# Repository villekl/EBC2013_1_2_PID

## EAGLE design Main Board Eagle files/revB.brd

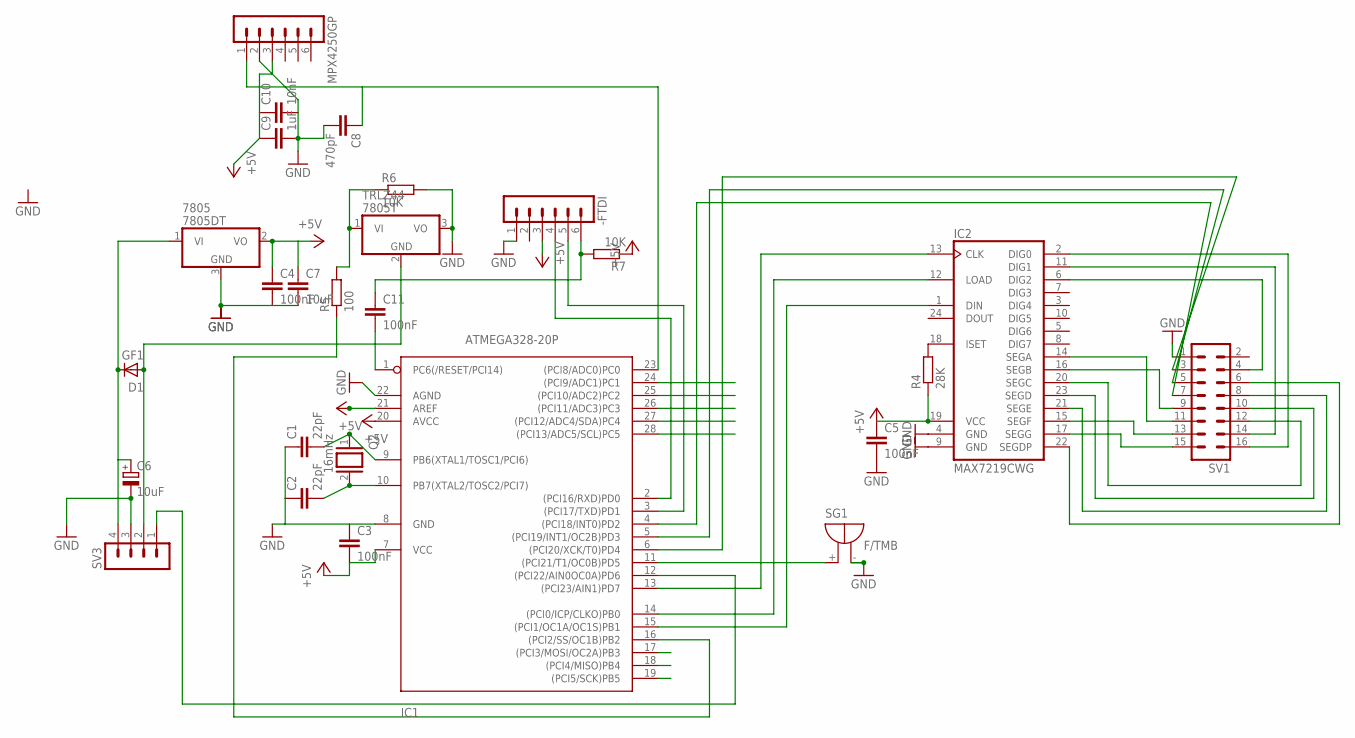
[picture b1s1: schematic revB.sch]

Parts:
7805: 7805DT; TO252
-FTDI: MA06-1
C1, C2: 22pF; C0805; MPN ERB21B5C2D220JDX1L
C3, C4, C5, C11: 100nF; C0805; MPN C0805X104K5RACTU
C6: 10uF; E2,5-6E
C7: 10uF; C0805; MPN C0805X104K5RACTU
C8: 470pF; C0805; MPN C0805X104K5RACTU
C9: 1uF; C0805; MPN C0805X104K5RACTU
C10: 10nF; C0805; MPN C0805X104K5RACTU
D1: GF1; SMA-DO214AC
IC1: ATMEGA328-20P; DIL28-3
IC2: MAX7219CWG
MPX4250GP: MA06-1
Q2: 16mHz; QS; MPN 16.000MHZ HC49/4H/30/50/40/18PF/ATF
R4: 28K; R0805
R5: 100; R0805
R6, R7: 10K; R0805
SG1: F/TMB
SV1: MA08-2
SV3: MA04-1
TRLZ44: 7805T; TO220H

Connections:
+5V: 7805.2 (VO), -FTDI.3, C3.2, C4.1, C5.1, C7.1, C9.1, C10.1, IC1.7 (VCC), IC1.20 (AVCC), IC1.21 (AREF), IC2.19 (VCC), MPX4250GP.3, R4.1, R7.1
GND: 7805.3 (GND), -FTDI.1, C1.1, C2.1, C3.1, C4.2, C5.2, C6.-, C7.2, C8.2, C9.2, C10.2, IC1.8 (GND), IC1.22 (AGND), IC2.4 (GND), IC2.9 (GND), MPX4250GP.2, R6.2, SG1.-, SV1.1, SV3.3, TRLZ44.3 (VO)
unnamed: C1.2, IC1.9 (PB6(XTAL1/TOSC1/PCI6)), Q2.1
unnamed: R5.2, R6.1, TRLZ44.1 (VI)
unnamed: IC1.15 ((PCI1/OC1A/OC1S)PB1), IC2.1 (DIN)
unnamed: IC2.6 (DIG2), SV1.4
unnamed: IC2.11 (DIG1), SV1.14
unnamed: IC2.22 (SEGDP), SV1.6
unnamed: IC2.21 (SEGE), SV1.8
unnamed: C8.1, IC1.23 ((PCI8/ADC0)PC0), MPX4250GP.1
unnamed: IC2.23 (SEGD), SV1.10
unnamed: IC2.20 (SEGC), SV1.12
unnamed: IC2.2 (DIG0), SV1.16
unnamed: IC2.17 (SEGG), SV1.15
unnamed: IC2.15 (SEGF), SV1.13
unnamed: IC2.14 (SEGA), SV1.11
unnamed: IC2.18 (ISET), R4.2
unnamed: IC1.16 ((PCI2/SS/OC1B)PB2), R5.1
unnamed: IC1.14 ((PCI0/ICP/CLKO)PB0), IC2.12 (LOAD)
unnamed: IC1.13 ((PCI23/AIN1)PD7), IC2.13 (CLK)
unnamed: IC1.4 ((PCI18/INT0)PD2), SV1.7
unnamed: IC1.5 ((PCI19/INT1/OC2B)PD3), SV1.5
unnamed: IC1.6 ((PCI20/XCK/T0)PD4), SV1.3
unnamed: IC1.11 ((PCI21/T1/OC0B)PD5), SG1.+
unnamed: -FTDI.6, C11.1, R7.2
unnamed: -FTDI.4, IC1.2 ((PCI16/RXD)PD0)
unnamed: -FTDI.5, IC1.3 ((PCI17/TXD)PD1)
unnamed: 7805.1 (VI), C6.+, D1.K (C), SV3.4
unnamed: C2.2, IC1.10 (PB7(XTAL2/TOSC2/PCI7)), Q2.2
unnamed: D1.A, SV3.2, TRLZ44.2 (GND)
unnamed: IC1.12 ((PCI22/AIN0OC0A)PD6), SV3.1
unnamed: IC2.16 (SEGB), SV1.9
unnamed: C11.2, IC1.1 (PC6(/RESET/PCI14))

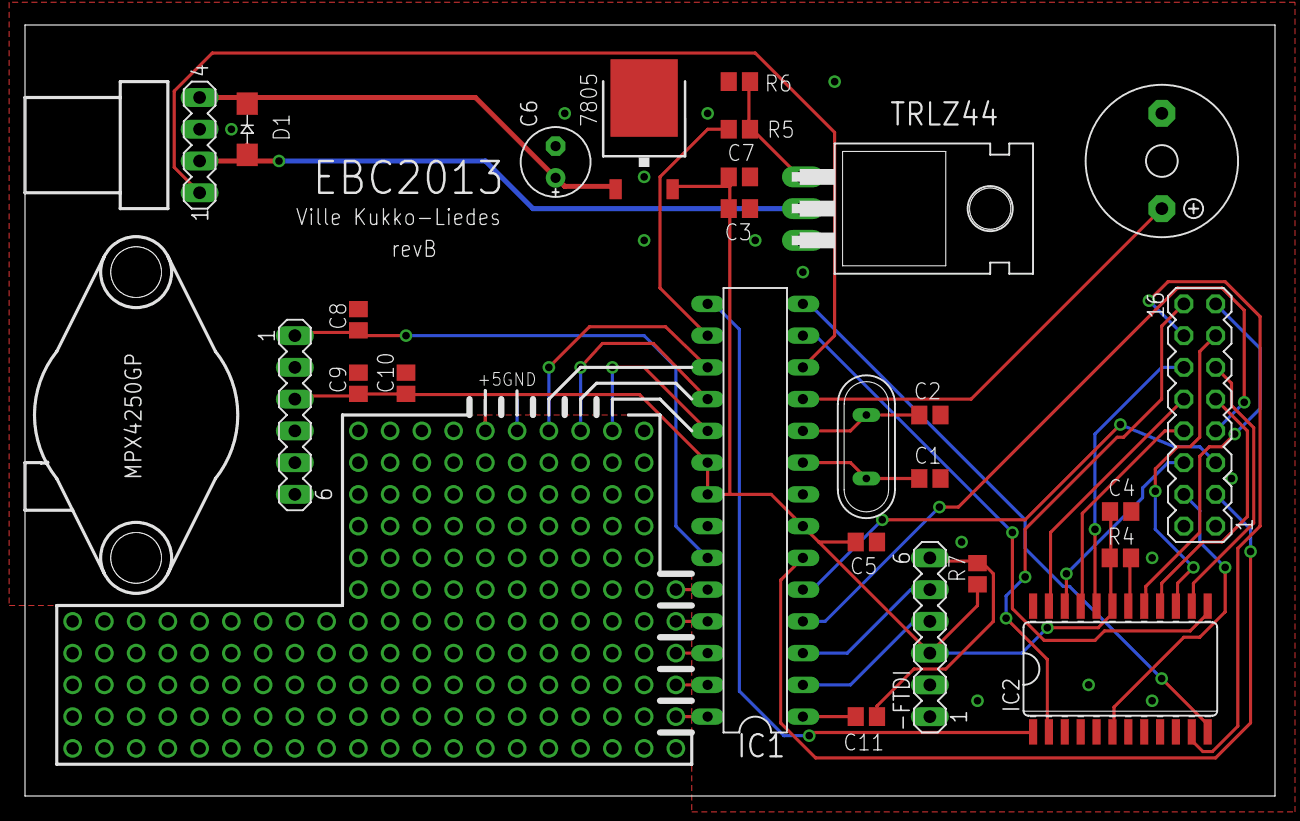
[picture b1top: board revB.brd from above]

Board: 2 copper layers, 100.0 x 61.7 mm, 26 parts (0 on the bottom side), 33 nets.

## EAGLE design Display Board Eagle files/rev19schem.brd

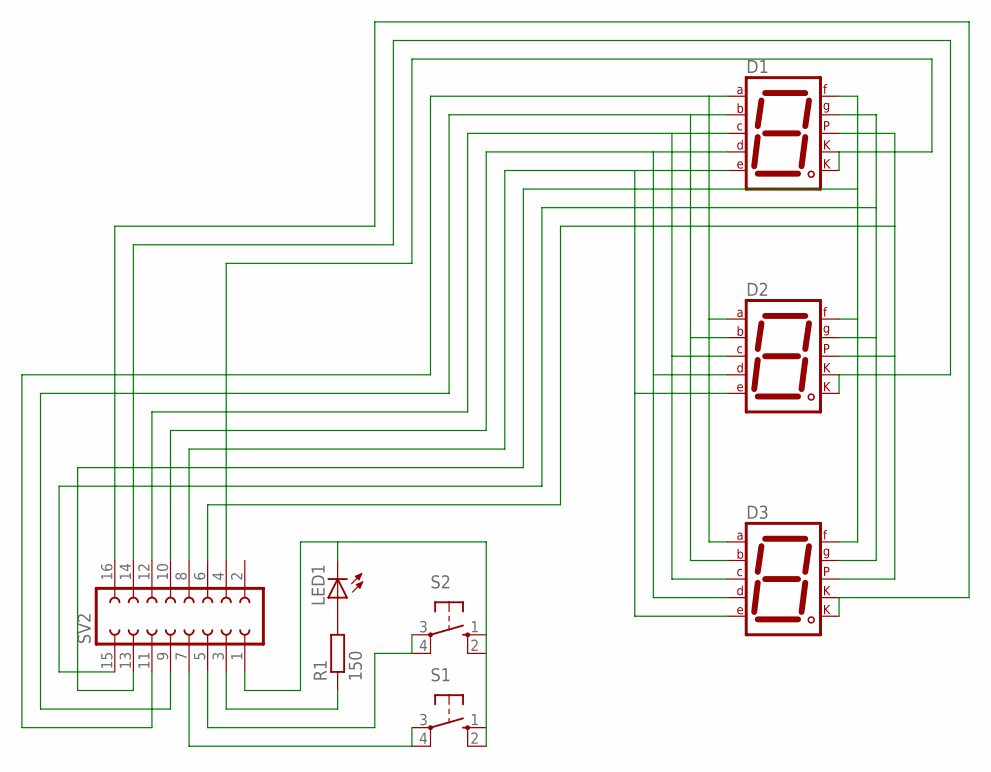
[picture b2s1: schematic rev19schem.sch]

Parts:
D1, D2, D3: 7SEG-CK; 7SEG-13
LED1: LED5MM
R1: 150; R0805
S1, S2: 10-XX; B3F-10XX
SV2: FE08-2

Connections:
unnamed: D1.6 (B), D2.6 (B), D3.6 (B), SV2.9
unnamed: D1.4 (C), D2.4 (C), D3.4 (C), SV2.12
unnamed: D1.2 (D), D2.2 (D), D3.2 (D), SV2.10
unnamed: D1.1 (E), D2.1 (E), D3.1 (E), SV2.8
unnamed: D1.9 (F), D2.9 (F), D3.9 (F), SV2.13
unnamed: D1.10 (G), D2.10 (G), D3.10 (G), SV2.15
unnamed: D1.5 (DP), D2.5 (DP), D3.5 (DP), SV2.6
unnamed: D1.3 (CK1), D1.8 (CK2), SV2.4
unnamed: D2.3 (CK1), D2.8 (CK2), SV2.14
unnamed: D3.3 (CK1), D3.8 (CK2), SV2.16
unnamed: D1.7 (A), D2.7 (A), D3.7 (A), SV2.11
unnamed: LED1.K (C), S1.1 (S), S1.2 (S1), S2.1 (S), S2.2 (S1), SV2.1
unnamed: LED1.A, R1.2
unnamed: R1.1, SV2.3
unnamed: S2.3, S2.4 (P1), SV2.5
unnamed: S1.3, S1.4 (P1), SV2.7

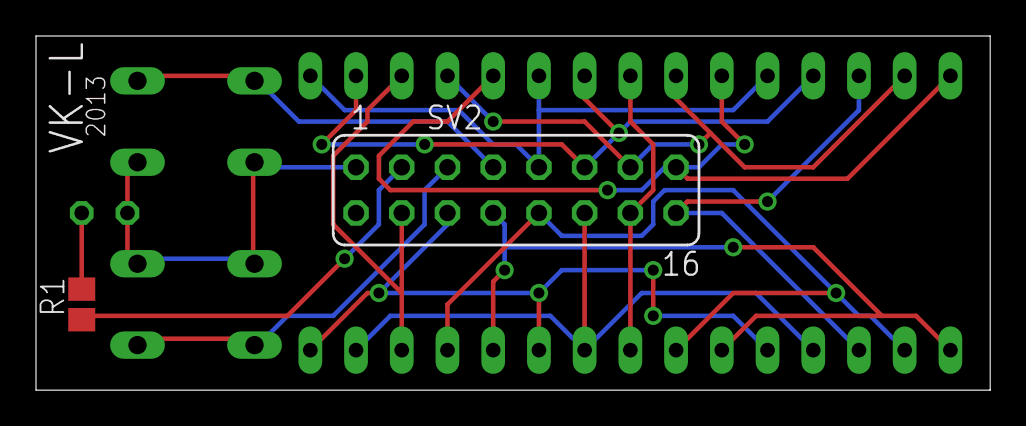
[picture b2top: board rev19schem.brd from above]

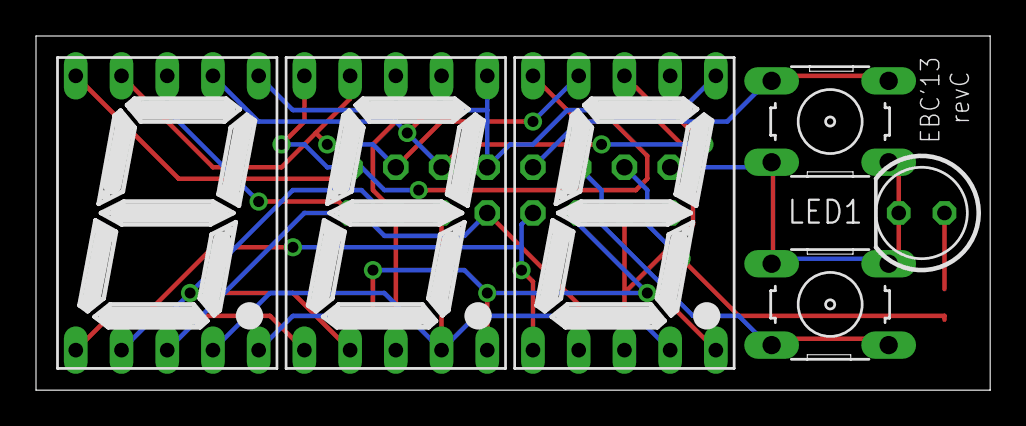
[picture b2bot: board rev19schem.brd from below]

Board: 2 copper layers, 53.0 x 19.7 mm, 8 parts (6 on the bottom side), 16 nets.

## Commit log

2014-01-20 EBC
    Arduino electronic boost controller
2014-01-22 Eagle files
2014-01-22 a
    a
2014-01-22 b
    b
